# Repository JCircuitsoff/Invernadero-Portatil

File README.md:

# Invernadero-Portatil
Invernadero pequeño que cuenta con distintos sensores, actuadores y un microcontrolador ESP32-DEVKIT-V1, que permiten realizar funciones de forma automatizada para el cuidado de un micro vegetal conocido como la rúcula o la rúgula.

Notas con respecto a la programación:

IDE utilizado: Thonny
Lenguaje de programacion: Micropython

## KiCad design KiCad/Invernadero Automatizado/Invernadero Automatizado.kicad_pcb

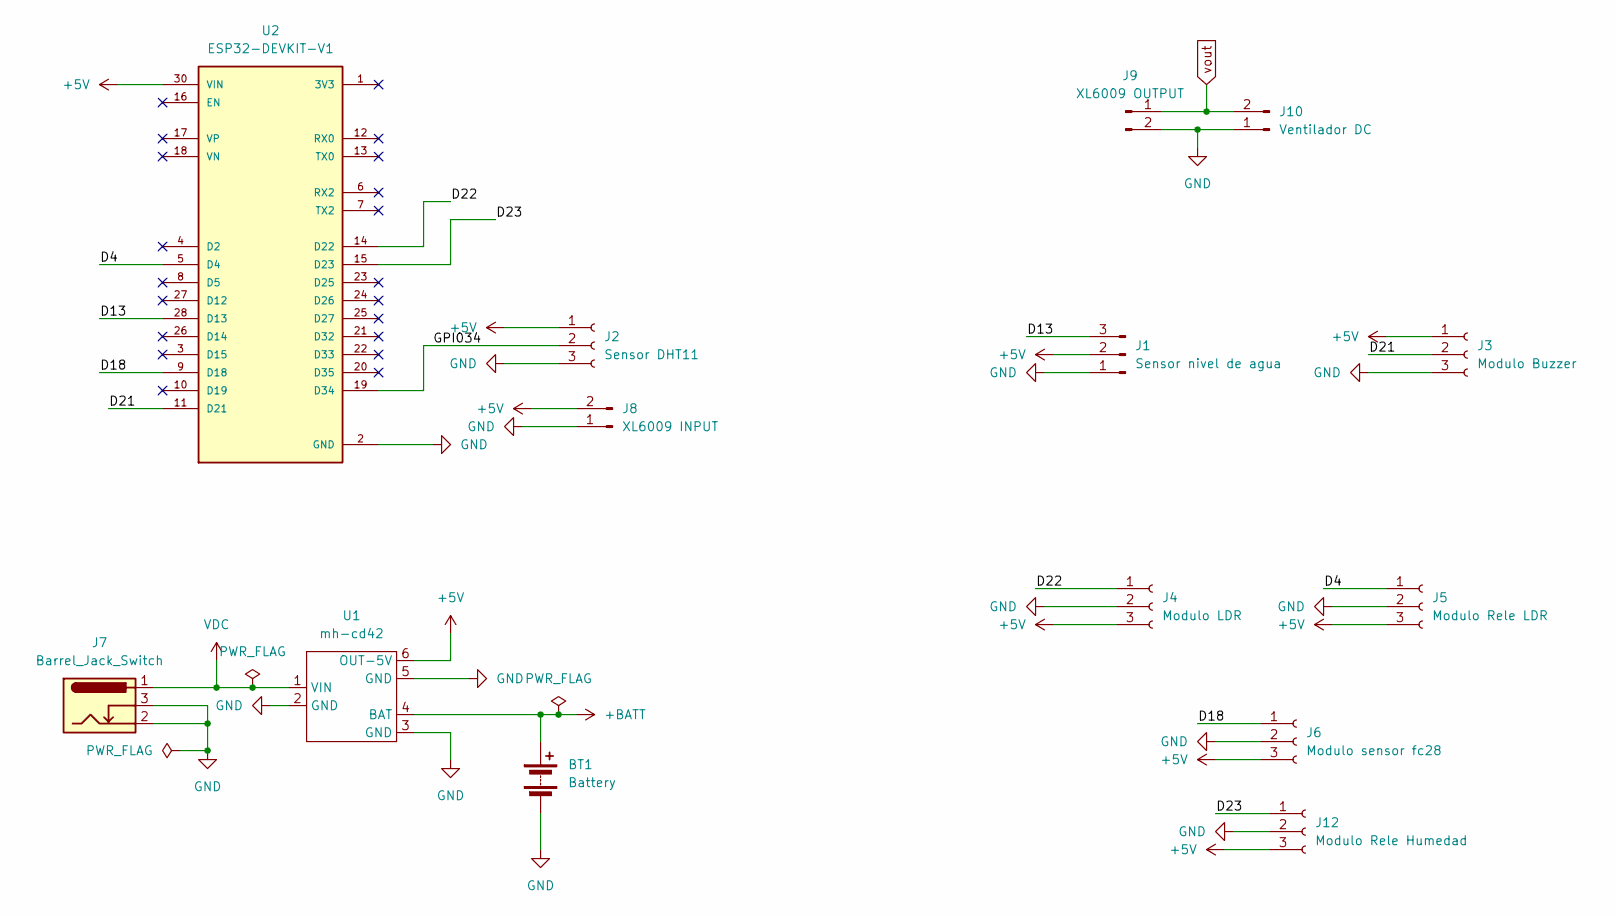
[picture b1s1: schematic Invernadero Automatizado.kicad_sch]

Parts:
BT1: Battery; BatteryHolder_Keystone_1042_1x18650
J1: Sensor nivel de agua; PinHeader_1x03_P2.54mm_Vertical
J2: Sensor DHT11; PinHeader_1x03_P2.54mm_Vertical
J3: Modulo Buzzer; PinSocket_1x03_P2.54mm_Vertical
J4: Modulo LDR; PinSocket_1x03_P2.54mm_Vertical
J5: Modulo Rele LDR; PinSocket_1x03_P2.54mm_Vertical
J6: Modulo sensor fc28; PinSocket_1x03_P2.54mm_Vertical
J7: Barrel_Jack_Switch; BarrelJack_Horizontal
J8: XL6009 INPUT; PinHeader_1x02_P2.54mm_Vertical
J9: XL6009 OUTPUT; PinHeader_1x02_P2.54mm_Vertical
J10: Ventilador DC; PinHeader_1x02_P2.54mm_Vertical
J12: Modulo Rele Humedad; PinSocket_1x03_P2.54mm_Vertical
U1: mh-cd42
U2: ESP32-DEVKIT-V1; MODULE_ESP32_DEVKIT_V1; PARTREV N/A

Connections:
+5V: J1.2, J2.1, J3.1, J4.3, J5.3, J6.3, J8.2, J12.3, U1.6 (OUT-5V), U2.30 (VIN)
+BATT: BT1.1 (+), U1.4 (BAT)
/D4: J5.1, U2.5 (D4)
/D13: J1.3, U2.28 (D13)
/D18: J6.1, U2.9 (D18)
/D21: J3.2, U2.11 (D21)
/D22: J4.1, U2.14 (D22)
/D23: J12.1, U2.15 (D23)
/GPI034: J2.2, U2.19 (D34)
GND: BT1.2 (-), J1.1, J2.3, J3.3, J4.2, J5.2, J6.2, J7.2, J7.3, J8.1, J9.2, J10.1, J12.2, U1.2 (GND), U1.3 (GND), U1.5 (GND), U2.2 (GND), U2.29 (GND)
VDC: J7.1, U1.1 (VIN)
vout: J9.1, J10.2

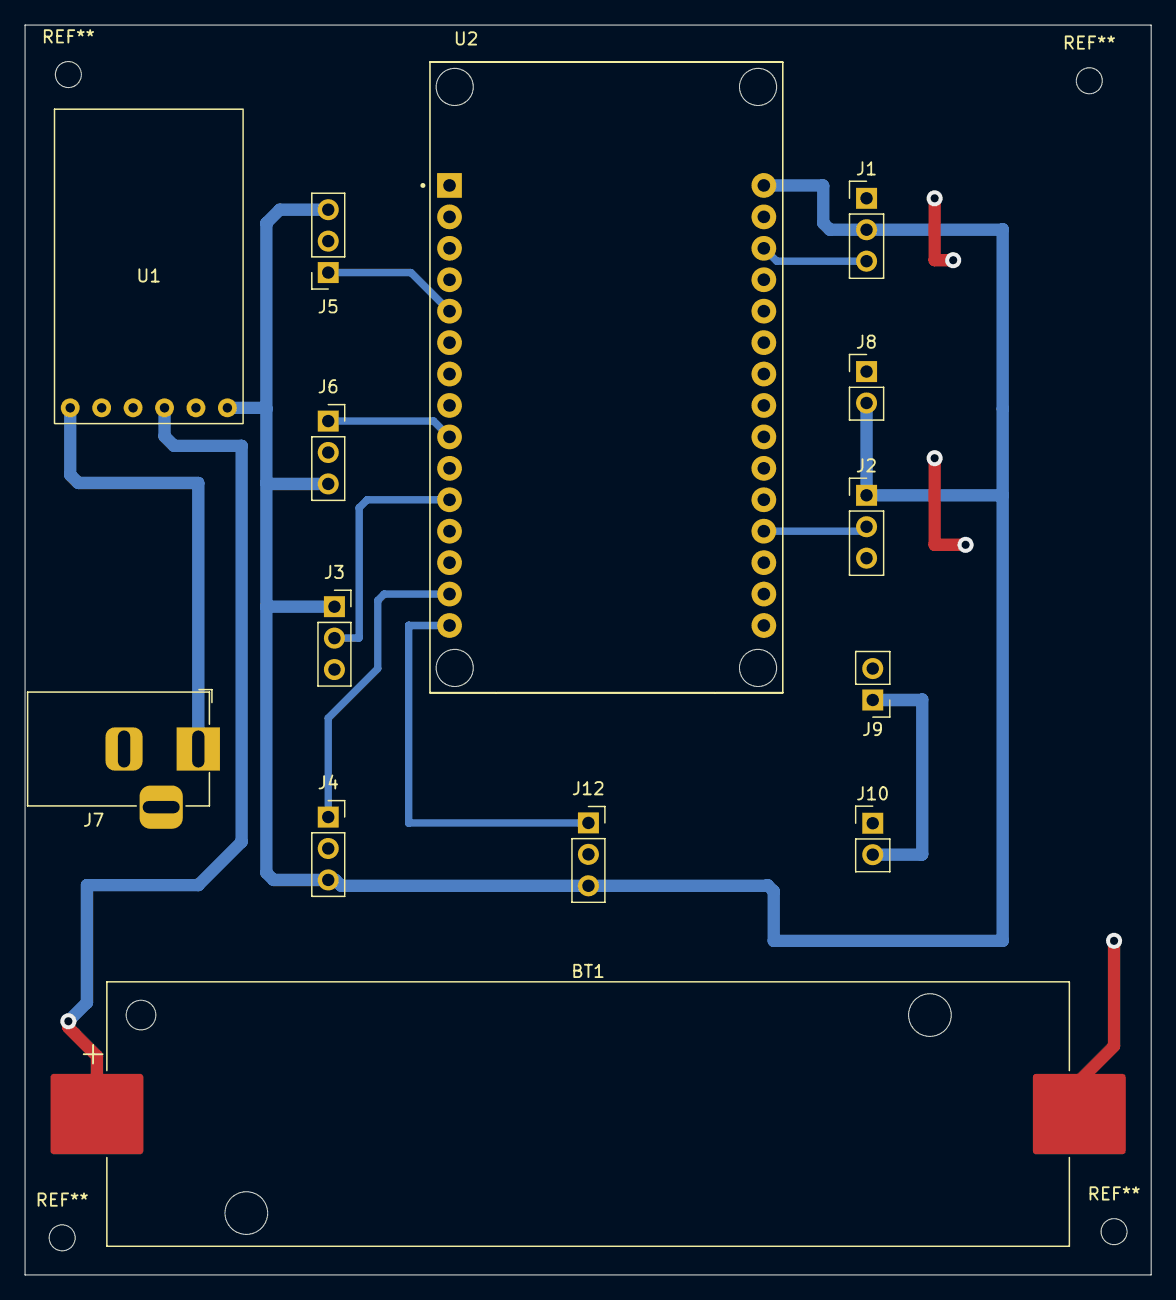
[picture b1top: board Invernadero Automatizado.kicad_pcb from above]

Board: 2 copper layers, 91.0 x 101.0 mm, 14 parts (0 on the bottom side), 12 nets.

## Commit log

2025-11-04 Diagramas
2025-11-04 Create Diagrama de flujo
2025-11-05 Create 1ra
2025-12-05 Create i
2025-12-09 Enhance README with project description and notes
    Added project details and programming notes.
2025-12-10 Create Esquemático
2025-12-10 Esquemático
2025-12-10 Create Si
2025-12-10 Create NO
2025-12-10 Create SAS
2025-12-10 Create Nao
2025-12-10 DeletAS
2025-12-10 Create Sis
2025-12-10 Fix formatting in README.md
2025-12-10 Create Po
2025-12-10 Create a
2025-12-10 Create f
